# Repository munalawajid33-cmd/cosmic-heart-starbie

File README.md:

# cosmic-heart-starbie
Heart shaped starbie

A heart-shaped, USB-powered desk pet. Shake it and the cat answers you.

Board:

Custom pixel-heart board outline (the guide uses a different shape)
Hand-drawn silkscreen art on the front and back: a cat with headphones, music notes, hearts, sparkles, a "Shake Me!" speech bubble and the name of the pet. my initials at the back are also included.
Layout redone so the buttons are mirrored in the two lobes of the heart, with the OLED at the bottom

Firmware (my own additions to Starbie.ino)

Cat Oracle: shake the board and the cat shows a message I wrote (purrfect, ask again, not today, ...) in a box at the top of the screen for 3 seconds
Temperature mood: uses the DHT11. The cat shows a sweat drop and "hot!" above 30 C, and "brr" below 18 C
Startup screen: shows my name and a twinkling star animation when it turns on
Screen saver: the screen dims after 30 seconds of no activity and turns off after 2 minutes. A button press or a shake wakes it
Sparkle trail: a blinking star behind the cat as it walks
My own sprites: a 32x32 cat I drew, plus a second sleepy version that shows during NAP
Renamed menu items (SNACK, PURR) to fit my cat

 Bill of Materials (BOM)

| Item | Qty | cost(BHD)| cost(dollars) | Source / Link |
| :--- | :--- | :---: | :---: | :--- |
| XIAO ESP32 C3 | 1 | 1.51 | $4 | https://www.temu.com/qa/goods.html?refer_share_id=75fc9b92-c4bb-438e-af53-1483c8a7&_bg_fs=1&goods_id=601099588295925&from_share=1&refer_share_channel=whatsapp_chat&_oak_page_source=417&_oak_region=16&refer_share_suin=RSSBDGQRZLB2XEHSOBQGA35DNQXU2SGXO3D6TZDVIGPLXNBRJ6W2HCNEDKNZMYYIOGHOC4UGNA&share_img=https%3A%2F%2Fimg-eu.kwcdn.com%2Fgoods-detail-img%2F35b7c2%2FyeUWmfsNGd%2F8f20f728a0fc4ab6bb9a5c6c68abbfc8.png&share_ui_type=1&_x_share_id=75fc9b92-c4bb-438e-af53-1483c8a7&refer_page_name=goods&refer_page_id=10032_1791736951229_8uj6zypgti&refer_page_sn=10032&_x_sessn_id=m8wxwrjlei |
| 0.96 OLED | 1 | 2.42 | $6.41 | https://share.temu.com/fo2B2snlRnB |
| MPU6050 | 1 | 4.95 | $13.12 | https://share.temu.com/gicZKMNHfUB |
| DHT11 | 1 | 3.19 | $8.19 | https://share.temu.com/oQAE6SqBJ5B |
| MX Switches | 2 | 3.95 | $10.47 | https://share.temu.com/Yso3pKZKMwB |
| Keycaps | 2 | 1.4 | $3.71 | https://share.temu.com/tN0pxzwWMbB |
| 10k resistor | 1 | 1.69 | $4.48 | https://share.temu.com/93UU8f7UntB |
| PCB | 1 | 3 | $7.95 | https://share.temu.com/TSFyHHeBl1B |

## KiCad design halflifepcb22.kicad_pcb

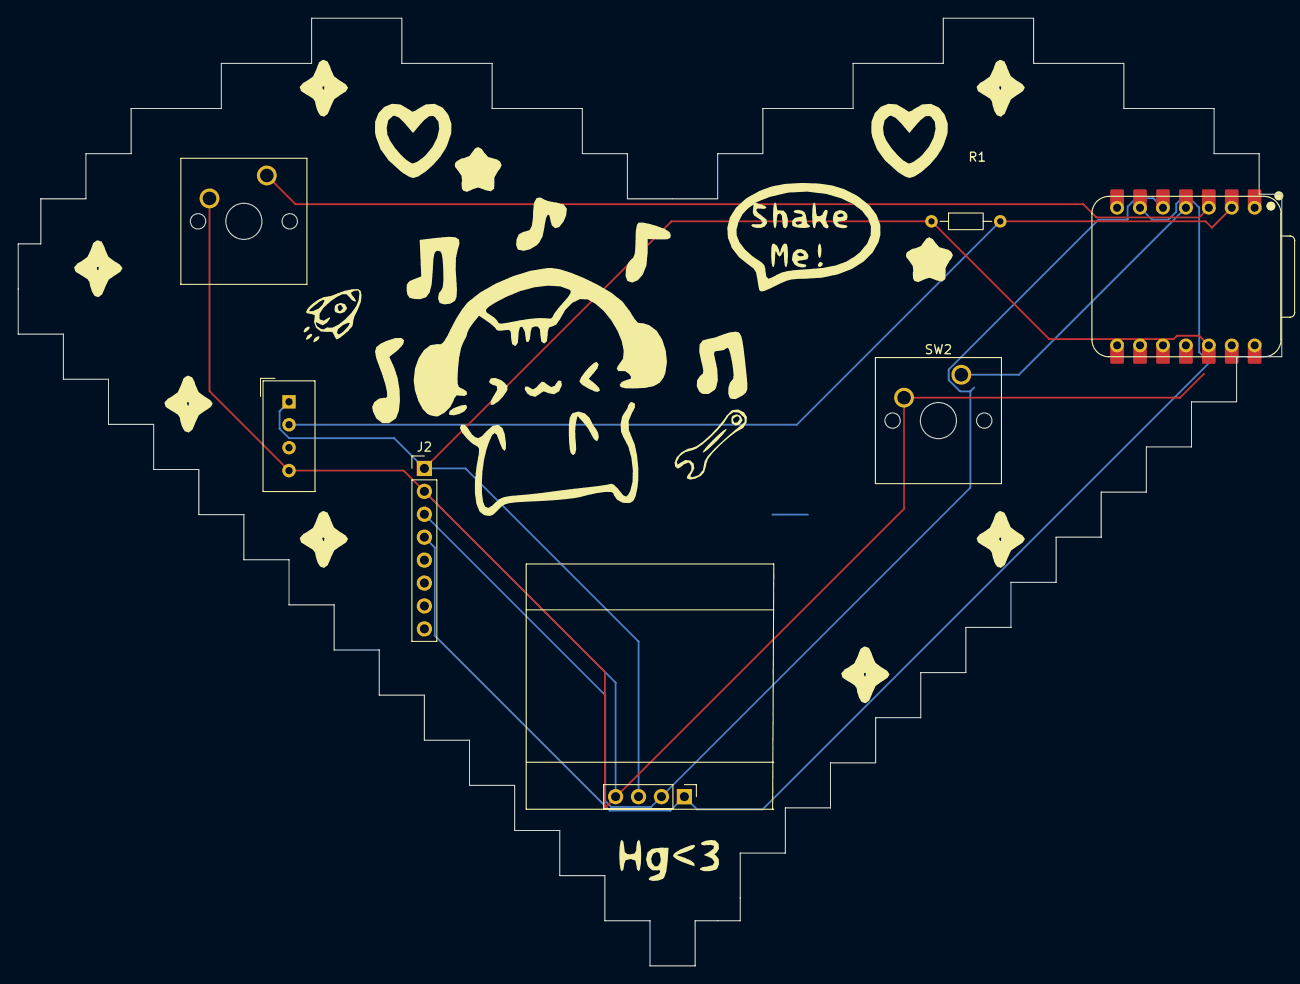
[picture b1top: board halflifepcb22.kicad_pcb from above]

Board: 2 copper layers, 140.0 x 105.0 mm, 7 parts (0 on the bottom side), 7 nets.

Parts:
J1: Conn_01x04_Pin; Display_128x64_096_I2C
J2: Conn_01x08_Pin; PinHeader_1x08_P2.54mm_Vertical
R1: 10k; R_Axial_DIN0204_L3.6mm_D1.6mm_P7.62mm_Horizontal
SW1, SW2: SW_Push; SW_Cherry_MX_1.00u_PCB
U1: XIAO-ESP32-C3-SMD; XIAO-ESP32-C6-DIP
U2: DHT11; Aosong_DHT11_5.5x12.0_P2.54mm

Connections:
+3.3V: J1.3, J2.1, R1.1, U1.12 (3V3_OUT), U2.1 (VDD)
/DHT11 DATA: R1.2, U1.2 (D1), U2.2 (DATA)
/GPIO2: SW1.1, U1.3 (D2)
/GPIO3: SW2.1, U1.4 (D3)
/SCL: J1.2, J2.3, U1.5 (D4)
/SDA: J1.1, J2.4, U1.6 (D5)
GND: J1.4, J2.2, SW1.2, SW2.2, U1.13 (GND), U2.4 (GND)
